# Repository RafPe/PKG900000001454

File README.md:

# Gumstix Raspberry Pi CM4 Uprev
## PKG900000001454 ![][thumbnail]

The **Gumstix Raspberry Pi CM4 Uprev** board allows the Raspberry Pi CM4 COM to be used on existing CM3 boards. The CM4's GPIOs, communications signals, and power pins are re-routed onto a SODIMM edge connection to match the pin-out of the CM3.

__Features Include__:
* Raspberry Pi CM3-compatible SODIMM edge connection
* Power indicator LED

__Links:__
* [AutoDoc Datasheet][autodoc]
* [Specifications][spec]
* [Store Page][store]
* [Schematics and Layout][hardware]

[thumbnail]: https://d3iwea566ns1n1.cloudfront.net/images/product/218b903c5c33ae7da5bafa5d72b35504696c6415.png
[autodoc]: PKG900000001454_AutoDoc.pdf
[spec]: PKG900000001454_SpecSheet.pdf
[store]: https://store.gumstix.com/cm4-uprev/
[hardware]: hardware/hardware.md
[firmware]: firmware/firmware.md

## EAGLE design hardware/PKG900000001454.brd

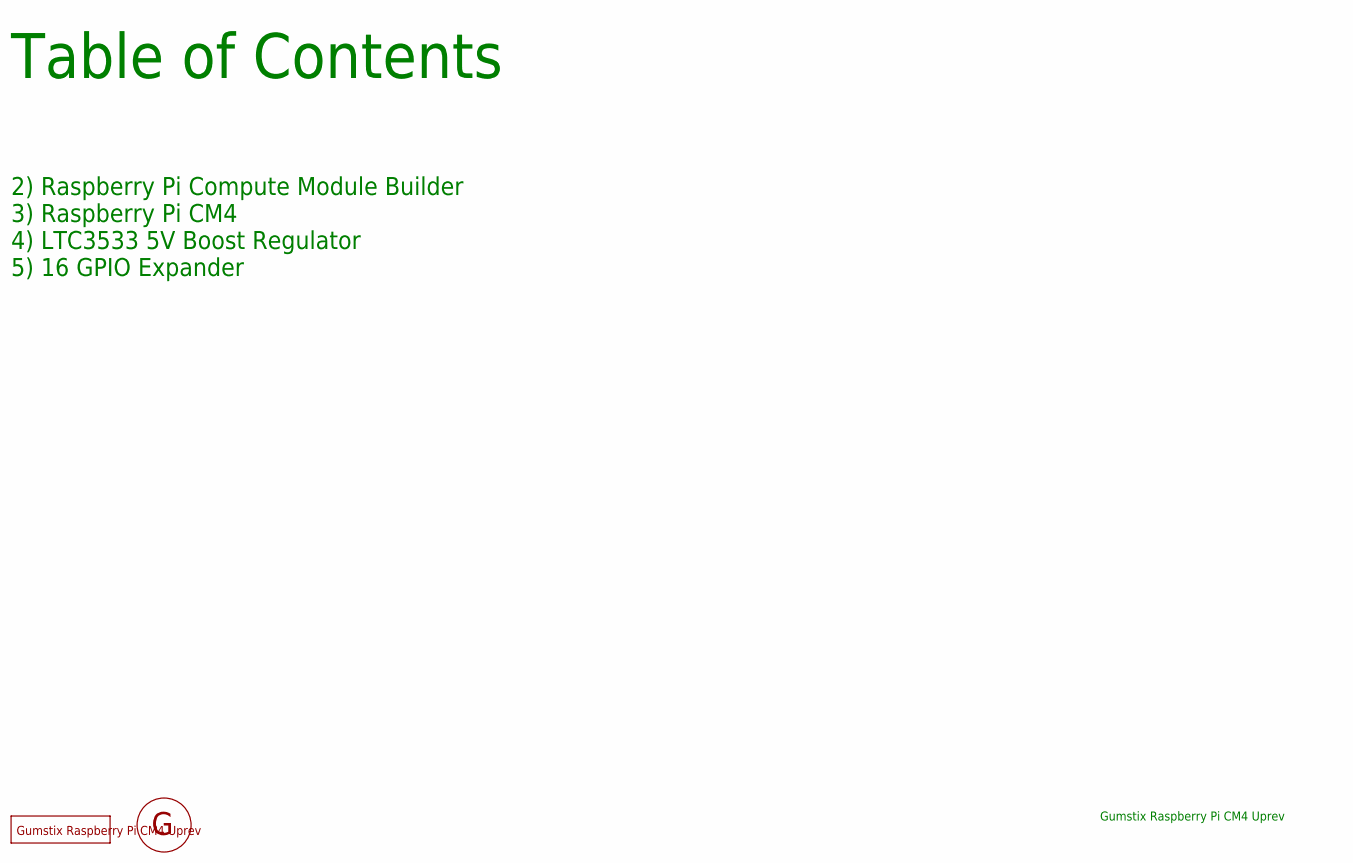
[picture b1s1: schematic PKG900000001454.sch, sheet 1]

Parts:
FD1, FD2, FD3, FD4, FD5, FD6: DNP; FIDUCIAL
U$3: DNP; GEPPETTO_LABEL
U$4: DNP; GEPPETTO_LOGO_SILK10

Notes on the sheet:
Table of Contents
Gumstix Raspberry Pi CM4 Uprev
2) Raspberry Pi Compute Module Builder
3) Raspberry Pi CM4
4) LTC3533 5V Boost Regulator
5) 16 GPIO Expander

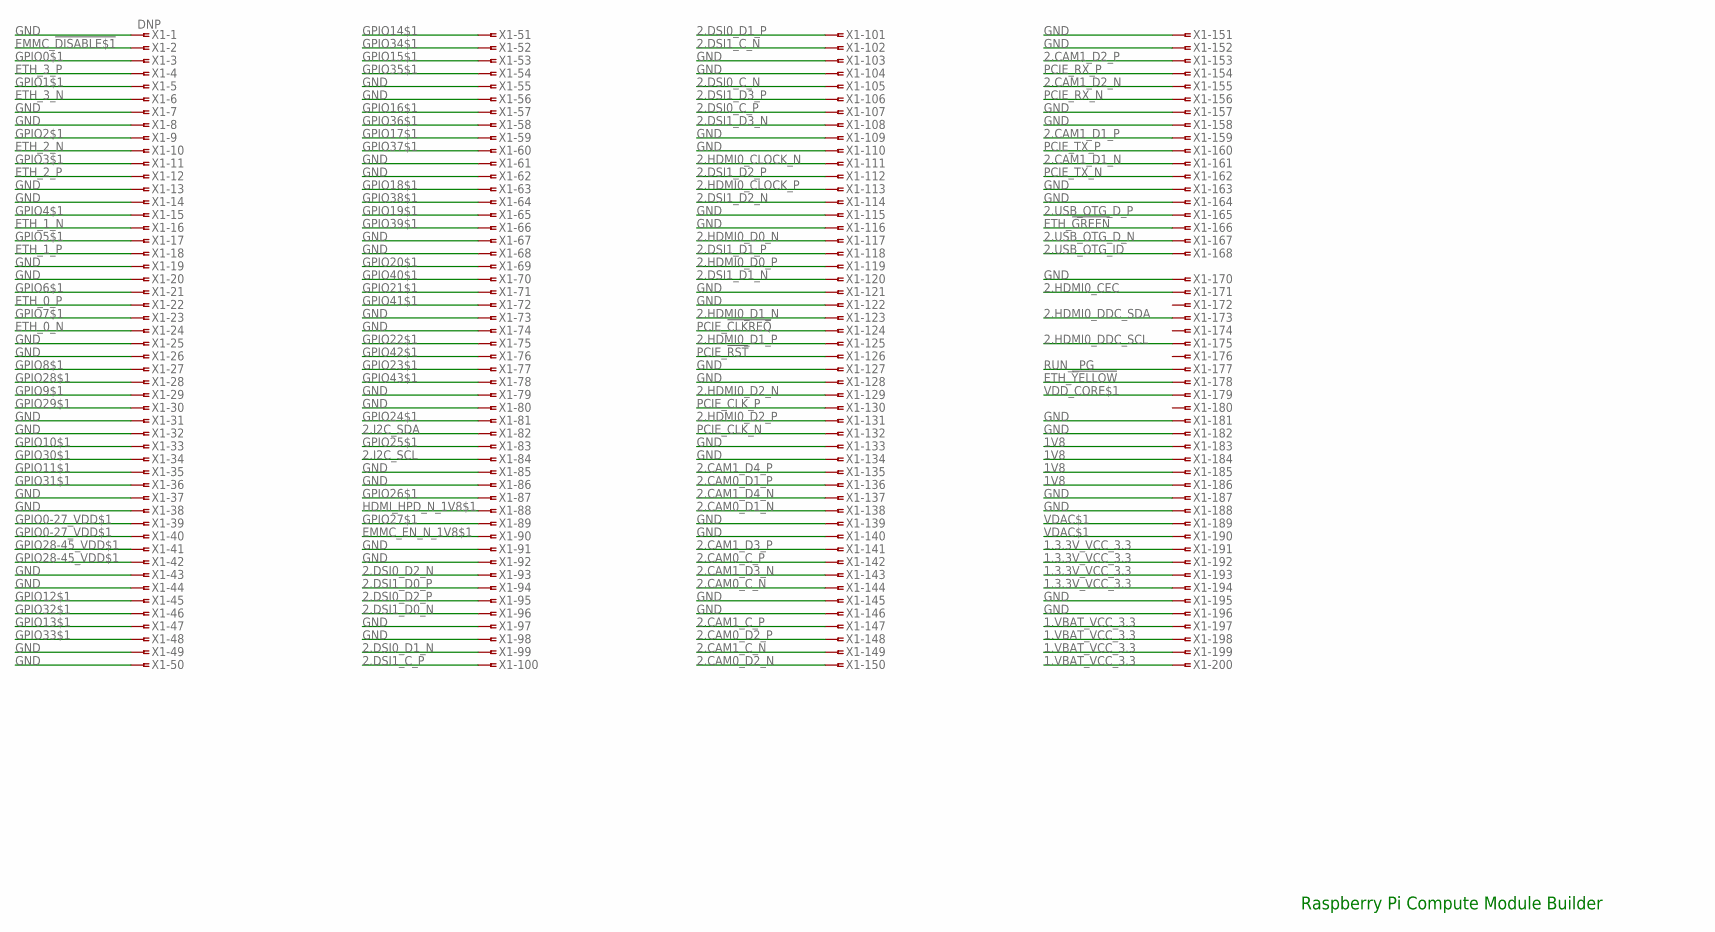
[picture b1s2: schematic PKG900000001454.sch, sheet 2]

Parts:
X1: DNP; SLOT-1376408-1_1.8V_MOD

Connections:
1.3.3V_VCC_3.3: X1.191, X1.192, X1.193, X1.194; also elsewhere on the board
1.VBAT_VCC_3.3: X1.197, X1.198, X1.199, X1.200; also elsewhere on the board
1V8: X1.183, X1.184, X1.185, X1.186
2.CAM0_C_N: X1.144; also elsewhere on the board
2.CAM0_C_P: X1.142; also elsewhere on the board
2.CAM0_D1_N: X1.138; also elsewhere on the board
2.CAM0_D1_P: X1.136; also elsewhere on the board
2.CAM0_D2_N: X1.150; also elsewhere on the board
2.CAM0_D2_P: X1.148; also elsewhere on the board
2.CAM1_C_N: X1.149; also elsewhere on the board
2.CAM1_C_P: X1.147; also elsewhere on the board
2.CAM1_D1_N: X1.161; also elsewhere on the board
2.CAM1_D1_P: X1.159; also elsewhere on the board
2.CAM1_D2_N: X1.155; also elsewhere on the board
2.CAM1_D2_P: X1.153; also elsewhere on the board
2.CAM1_D3_N: X1.143; also elsewhere on the board
2.CAM1_D3_P: X1.141; also elsewhere on the board
2.CAM1_D4_N: X1.137; also elsewhere on the board
2.CAM1_D4_P: X1.135; also elsewhere on the board
2.DSI0_C_N: X1.105; also elsewhere on the board
2.DSI0_C_P: X1.107; also elsewhere on the board
2.DSI0_D1_N: X1.99; also elsewhere on the board
2.DSI0_D1_P: X1.101; also elsewhere on the board
2.DSI0_D2_N: X1.93; also elsewhere on the board
2.DSI0_D2_P: X1.95; also elsewhere on the board
2.DSI1_C_N: X1.102; also elsewhere on the board
2.DSI1_C_P: X1.100; also elsewhere on the board
2.DSI1_D0_N: X1.96; also elsewhere on the board
2.DSI1_D0_P: X1.94; also elsewhere on the board
2.DSI1_D1_N: X1.120; also elsewhere on the board
2.DSI1_D1_P: X1.118; also elsewhere on the board
2.DSI1_D2_N: X1.114; also elsewhere on the board
2.DSI1_D2_P: X1.112; also elsewhere on the board
2.DSI1_D3_N: X1.108; also elsewhere on the board
2.DSI1_D3_P: X1.106; also elsewhere on the board
2.HDMI0_CEC: X1.171; also elsewhere on the board
2.HDMI0_CLOCK_N: X1.111; also elsewhere on the board
2.HDMI0_CLOCK_P: X1.113; also elsewhere on the board
2.HDMI0_D0_N: X1.117; also elsewhere on the board
2.HDMI0_D0_P: X1.119; also elsewhere on the board
2.HDMI0_D1_N: X1.123; also elsewhere on the board
2.HDMI0_D1_P: X1.125; also elsewhere on the board
2.HDMI0_D2_N: X1.129; also elsewhere on the board
2.HDMI0_D2_P: X1.131; also elsewhere on the board
2.HDMI0_DDC_SCL: X1.175; also elsewhere on the board
2.HDMI0_DDC_SDA: X1.173; also elsewhere on the board
2.I2C_SCL: X1.84; also elsewhere on the board
2.I2C_SDA: X1.82; also elsewhere on the board
2.USB_OTG_D_N: X1.167; also elsewhere on the board
2.USB_OTG_D_P: X1.165; also elsewhere on the board
2.USB_OTG_ID: X1.168; also elsewhere on the board
EMMC_!DISABLE$1: X1.2; also elsewhere on the board
EMMC_EN_N_1V8$1: X1.90
ETH_0_N: X1.24; also elsewhere on the board
ETH_0_P: X1.22; also elsewhere on the board
ETH_1_N: X1.16; also elsewhere on the board
ETH_1_P: X1.18; also elsewhere on the board
ETH_2_N: X1.10; also elsewhere on the board
ETH_2_P: X1.12; also elsewhere on the board
ETH_3_N: X1.6; also elsewhere on the board
ETH_3_P: X1.4; also elsewhere on the board
ETH_!GREEN: X1.166; also elsewhere on the board
ETH_!YELLOW: X1.178; also elsewhere on the board
GND: X1.1, X1.7, X1.8, X1.13, X1.14, X1.19, X1.20, X1.25, X1.26, X1.31, X1.32, X1.37, X1.38, X1.43, X1.44, X1.49, X1.50, X1.55, X1.56, X1.61, X1.62, X1.67, X1.68, X1.73, X1.74, X1.79, X1.80, X1.85, X1.86, X1.91, X1.92, X1.97, X1.98, X1.103, X1.104, X1.109, X1.110, X1.115, X1.116, X1.121, X1.122, X1.127, X1.128, X1.133, X1.134, X1.139, X1.140, X1.145, X1.146, X1.151, X1.152, X1.157, X1.158, X1.163, X1.164, X1.170, X1.181, X1.182, X1.187, X1.188, X1.195, X1.196; also elsewhere on the board
GPIO0$1: X1.3; also elsewhere on the board
GPIO0-27_VDD$1: X1.39, X1.40
GPIO1$1: X1.5; also elsewhere on the board
GPIO2$1: X1.9; also elsewhere on the board
GPIO3$1: X1.11; also elsewhere on the board
GPIO4$1: X1.15; also elsewhere on the board
GPIO5$1: X1.17; also elsewhere on the board
GPIO6$1: X1.21; also elsewhere on the board
GPIO7$1: X1.23; also elsewhere on the board
GPIO8$1: X1.27; also elsewhere on the board
GPIO9$1: X1.29; also elsewhere on the board
GPIO10$1: X1.33; also elsewhere on the board
GPIO11$1: X1.35; also elsewhere on the board
GPIO12$1: X1.45; also elsewhere on the board
GPIO13$1: X1.47; also elsewhere on the board
GPIO14$1: X1.51; also elsewhere on the board
GPIO15$1: X1.53; also elsewhere on the board
GPIO16$1: X1.57; also elsewhere on the board
GPIO17$1: X1.59; also elsewhere on the board
GPIO18$1: X1.63; also elsewhere on the board
GPIO19$1: X1.65; also elsewhere on the board
GPIO20$1: X1.69; also elsewhere on the board
GPIO21$1: X1.71; also elsewhere on the board
GPIO22$1: X1.75; also elsewhere on the board
GPIO23$1: X1.77; also elsewhere on the board
GPIO24$1: X1.81; also elsewhere on the board
GPIO25$1: X1.83; also elsewhere on the board
GPIO26$1: X1.87; also elsewhere on the board
GPIO27$1: X1.89; also elsewhere on the board
GPIO28$1: X1.28; also elsewhere on the board
GPIO28-45_VDD$1: X1.41, X1.42
GPIO29$1: X1.30; also elsewhere on the board
GPIO30$1: X1.34; also elsewhere on the board
GPIO31$1: X1.36; also elsewhere on the board
GPIO32$1: X1.46; also elsewhere on the board
GPIO33$1: X1.48; also elsewhere on the board
GPIO34$1: X1.52; also elsewhere on the board
GPIO35$1: X1.54; also elsewhere on the board
GPIO36$1: X1.58; also elsewhere on the board
GPIO37$1: X1.60; also elsewhere on the board
GPIO38$1: X1.64; also elsewhere on the board
GPIO39$1: X1.66; also elsewhere on the board
GPIO40$1: X1.70; also elsewhere on the board
GPIO41$1: X1.72; also elsewhere on the board
GPIO42$1: X1.76; also elsewhere on the board
GPIO43$1: X1.78; also elsewhere on the board
HDMI_HPD_N_1V8$1: X1.88; also elsewhere on the board
PCIE_!CLKREQ: X1.124; also elsewhere on the board
PCIE_!RST: X1.126; also elsewhere on the board
PCIE_CLK_N: X1.132; also elsewhere on the board
PCIE_CLK_P: X1.130; also elsewhere on the board
PCIE_RX_N: X1.156; also elsewhere on the board
PCIE_RX_P: X1.154; also elsewhere on the board
PCIE_TX_N: X1.162; also elsewhere on the board
PCIE_TX_P: X1.160; also elsewhere on the board
RUN__PG: X1.177; also elsewhere on the board
VDAC$1: X1.189, X1.190
VDD_CORE$1: X1.179

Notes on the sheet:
Raspberry Pi Compute Module Builder

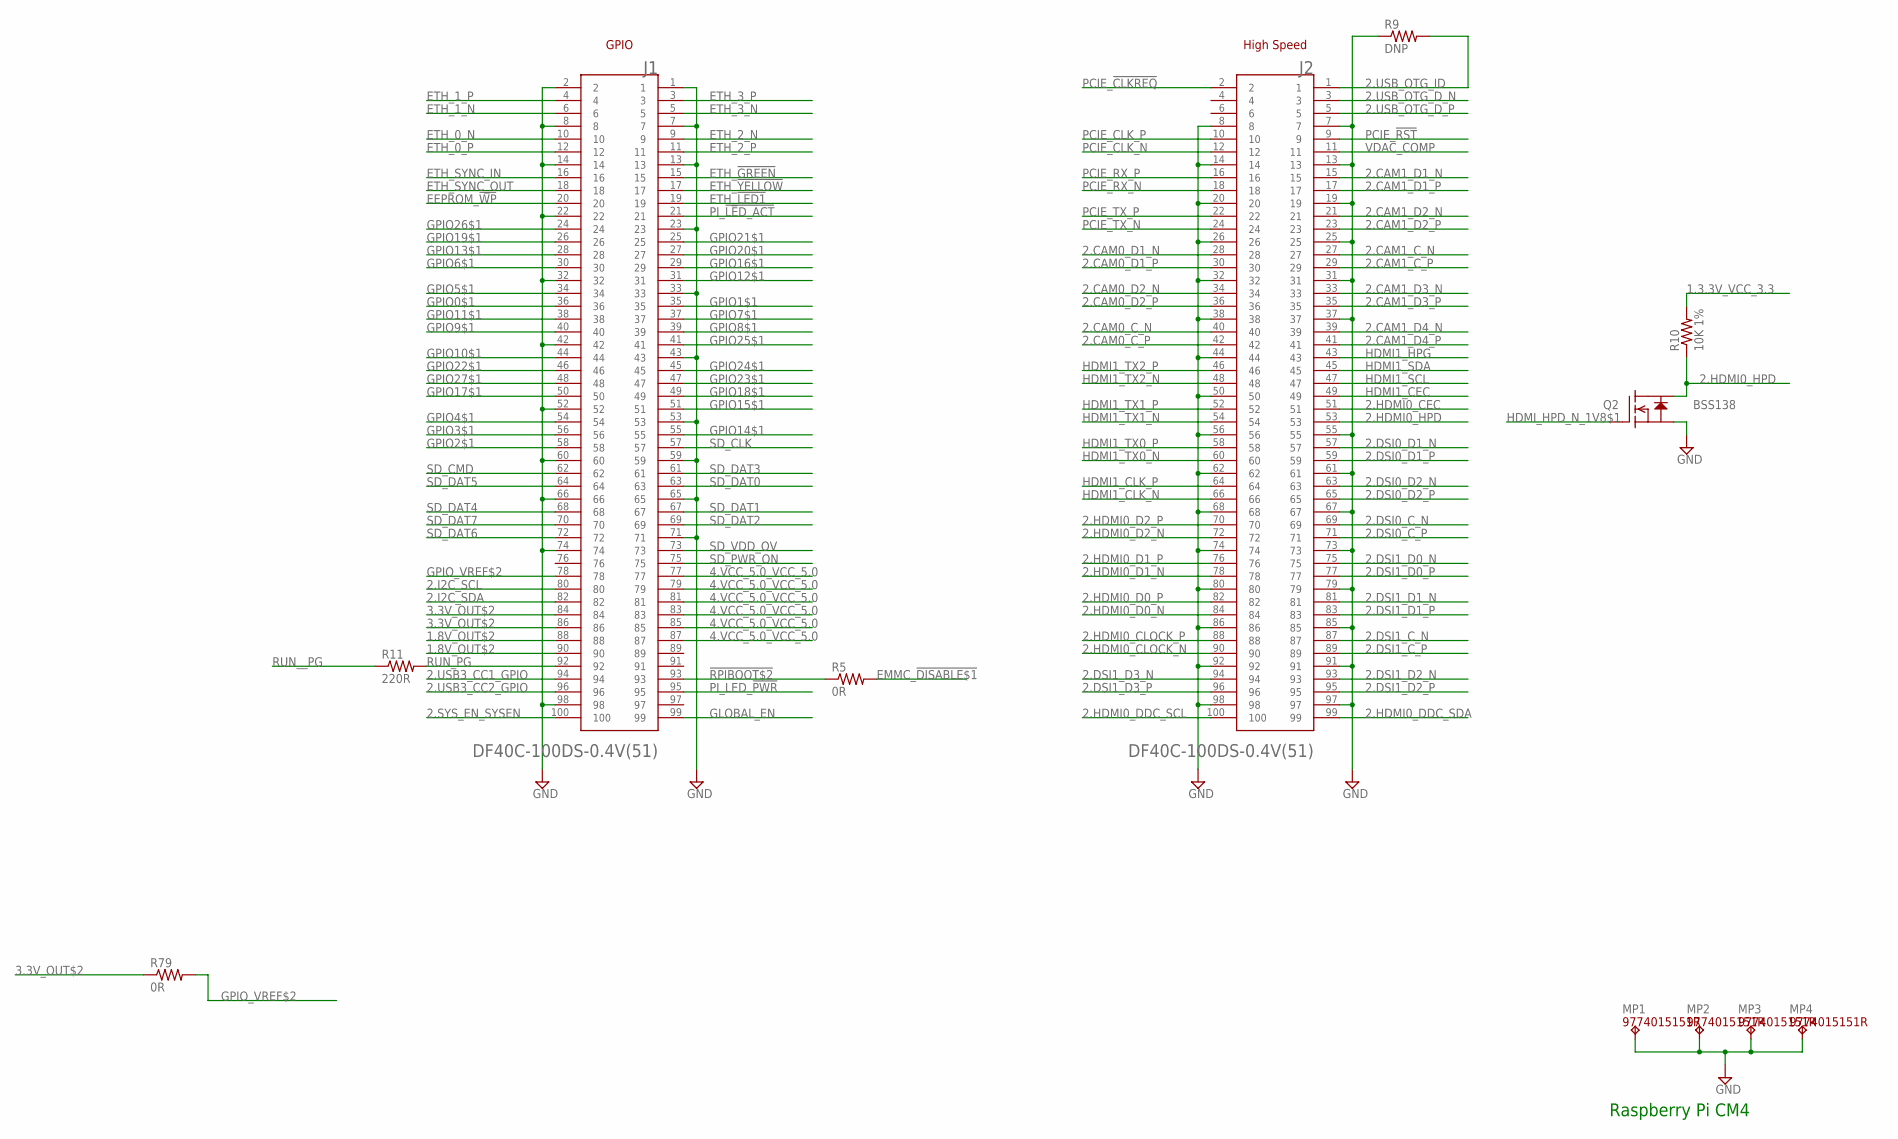
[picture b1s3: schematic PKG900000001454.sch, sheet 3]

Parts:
J1, J2: DF40C-100DS-0.4V(51); HRS_DF40C-100DS-0.4V(51)
MP1, MP2, MP3, MP4: 9774015151R; WA-SMSI_9774___151
Q2: BSS138; SOT23
R5, R79: 0R; 0201
R9: DNP; 0201
R10: 10K 1%; 0201
R11: 220R; 0402

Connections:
1.3.3V_VCC_3.3: R10.2; also elsewhere on the board
1.8V_OUT$2: J1.88, J1.90
2.CAM0_C_N: J2.40; also elsewhere on the board
2.CAM0_C_P: J2.42; also elsewhere on the board
2.CAM0_D1_N: J2.28; also elsewhere on the board
2.CAM0_D1_P: J2.30; also elsewhere on the board
2.CAM0_D2_N: J2.34; also elsewhere on the board
2.CAM0_D2_P: J2.36; also elsewhere on the board
2.CAM1_C_N: J2.27; also elsewhere on the board
2.CAM1_C_P: J2.29; also elsewhere on the board
2.CAM1_D1_N: J2.15; also elsewhere on the board
2.CAM1_D1_P: J2.17; also elsewhere on the board
2.CAM1_D2_N: J2.21; also elsewhere on the board
2.CAM1_D2_P: J2.23; also elsewhere on the board
2.CAM1_D3_N: J2.33; also elsewhere on the board
2.CAM1_D3_P: J2.35; also elsewhere on the board
2.CAM1_D4_N: J2.39; also elsewhere on the board
2.CAM1_D4_P: J2.41; also elsewhere on the board
2.DSI0_C_N: J2.69; also elsewhere on the board
2.DSI0_C_P: J2.71; also elsewhere on the board
2.DSI0_D1_N: J2.57; also elsewhere on the board
2.DSI0_D1_P: J2.59; also elsewhere on the board
2.DSI0_D2_N: J2.63; also elsewhere on the board
2.DSI0_D2_P: J2.65; also elsewhere on the board
2.DSI1_C_N: J2.87; also elsewhere on the board
2.DSI1_C_P: J2.89; also elsewhere on the board
2.DSI1_D0_N: J2.75; also elsewhere on the board
2.DSI1_D0_P: J2.77; also elsewhere on the board
2.DSI1_D1_N: J2.81; also elsewhere on the board
2.DSI1_D1_P: J2.83; also elsewhere on the board
2.DSI1_D2_N: J2.93; also elsewhere on the board
2.DSI1_D2_P: J2.95; also elsewhere on the board
2.DSI1_D3_N: J2.94; also elsewhere on the board
2.DSI1_D3_P: J2.96; also elsewhere on the board
2.HDMI0_CEC: J2.51; also elsewhere on the board
2.HDMI0_CLOCK_N: J2.90; also elsewhere on the board
2.HDMI0_CLOCK_P: J2.88; also elsewhere on the board
2.HDMI0_D0_N: J2.84; also elsewhere on the board
2.HDMI0_D0_P: J2.82; also elsewhere on the board
2.HDMI0_D1_N: J2.78; also elsewhere on the board
2.HDMI0_D1_P: J2.76; also elsewhere on the board
2.HDMI0_D2_N: J2.72; also elsewhere on the board
2.HDMI0_D2_P: J2.70; also elsewhere on the board
2.HDMI0_DDC_SCL: J2.100; also elsewhere on the board
2.HDMI0_DDC_SDA: J2.99; also elsewhere on the board
2.HDMI0_HPD: J2.53, Q2.3 (D), R10.1
2.I2C_SCL: J1.80; also elsewhere on the board
2.I2C_SDA: J1.82; also elsewhere on the board
2.SYS_EN_SYSEN: J1.100
2.USB3_CC1_GPIO: J1.94
2.USB3_CC2_GPIO: J1.96
2.USB_OTG_D_N: J2.3; also elsewhere on the board
2.USB_OTG_D_P: J2.5; also elsewhere on the board
2.USB_OTG_ID: J2.1, R9.2; also elsewhere on the board
3.3V_OUT$2: J1.84, J1.86, R79.1
4.VCC_5.0_VCC_5.0: J1.77, J1.79, J1.81, J1.83, J1.85, J1.87; also elsewhere on the board
!RPIBOOT$2: J1.93, R5.1
EEPROM_!WP: J1.20
EMMC_!DISABLE$1: R5.2; also elsewhere on the board
ETH_0_N: J1.10; also elsewhere on the board
ETH_0_P: J1.12; also elsewhere on the board
ETH_1_N: J1.6; also elsewhere on the board
ETH_1_P: J1.4; also elsewhere on the board
ETH_2_N: J1.9; also elsewhere on the board
ETH_2_P: J1.11; also elsewhere on the board
ETH_3_N: J1.5; also elsewhere on the board
ETH_3_P: J1.3; also elsewhere on the board
ETH_!GREEN: J1.15; also elsewhere on the board
ETH_!LED1: J1.19
ETH_!YELLOW: J1.17; also elsewhere on the board
ETH_SYNC_IN: J1.16
ETH_SYNC_OUT: J1.18
GLOBAL_EN: J1.99
GND: J1.1, J1.2, J1.7, J1.8, J1.13, J1.14, J1.22, J1.23, J1.32, J1.33, J1.42, J1.43, J1.52, J1.53, J1.59, J1.60, J1.65, J1.66, J1.71, J1.74, J1.98, J2.7, J2.8, J2.13, J2.14, J2.19, J2.20, J2.25, J2.26, J2.31, J2.32, J2.37, J2.38, J2.44, J2.50, J2.55, J2.56, J2.61, J2.62, J2.67, J2.68, J2.73, J2.74, J2.79, J2.80, J2.85, J2.86, J2.91, J2.92, J2.97, J2.98, MP1.1, MP2.1, MP3.1, MP4.1, Q2.2 (S), R9.1; also elsewhere on the board
GPIO0$1: J1.36; also elsewhere on the board
GPIO1$1: J1.35; also elsewhere on the board
GPIO2$1: J1.58; also elsewhere on the board
GPIO3$1: J1.56; also elsewhere on the board
GPIO4$1: J1.54; also elsewhere on the board
GPIO5$1: J1.34; also elsewhere on the board
GPIO6$1: J1.30; also elsewhere on the board
GPIO7$1: J1.37; also elsewhere on the board
GPIO8$1: J1.39; also elsewhere on the board
GPIO9$1: J1.40; also elsewhere on the board
GPIO10$1: J1.44; also elsewhere on the board
GPIO11$1: J1.38; also elsewhere on the board
GPIO12$1: J1.31; also elsewhere on the board
GPIO13$1: J1.28; also elsewhere on the board
GPIO14$1: J1.55; also elsewhere on the board
GPIO15$1: J1.51; also elsewhere on the board
GPIO16$1: J1.29; also elsewhere on the board
GPIO17$1: J1.50; also elsewhere on the board
GPIO18$1: J1.49; also elsewhere on the board
GPIO19$1: J1.26; also elsewhere on the board
GPIO20$1: J1.27; also elsewhere on the board
GPIO21$1: J1.25; also elsewhere on the board
GPIO22$1: J1.46; also elsewhere on the board
GPIO23$1: J1.47; also elsewhere on the board
GPIO24$1: J1.45; also elsewhere on the board
GPIO25$1: J1.41; also elsewhere on the board
GPIO26$1: J1.24; also elsewhere on the board
GPIO27$1: J1.48; also elsewhere on the board
GPIO_VREF$2: J1.78, R79.2
HDMI1_CEC: J2.49
HDMI1_CLK_N: J2.66
HDMI1_CLK_P: J2.64
HDMI1_HPG: J2.43
HDMI1_SCL: J2.47
HDMI1_SDA: J2.45
HDMI1_TX0_N: J2.60
HDMI1_TX0_P: J2.58
HDMI1_TX1_N: J2.54
HDMI1_TX1_P: J2.52
HDMI1_TX2_N: J2.48
HDMI1_TX2_P: J2.46
HDMI_HPD_N_1V8$1: Q2.1 (G); also elsewhere on the board
PCIE_!CLKREQ: J2.2; also elsewhere on the board
PCIE_!RST: J2.9; also elsewhere on the board
PCIE_CLK_N: J2.12; also elsewhere on the board
PCIE_CLK_P: J2.10; also elsewhere on the board
PCIE_RX_N: J2.18; also elsewhere on the board
PCIE_RX_P: J2.16; also elsewhere on the board
PCIE_TX_N: J2.24; also elsewhere on the board
PCIE_TX_P: J2.22; also elsewhere on the board
PI_!LED_ACT: J1.21
PI_LED_!PWR: J1.95
RUN_PG: J1.92, R11.2
RUN__PG: R11.1; also elsewhere on the board
SD_CLK: J1.57
SD_CMD: J1.62
SD_DAT0: J1.63
SD_DAT1: J1.67
SD_DAT2: J1.69
SD_DAT3: J1.61
SD_DAT4: J1.68
SD_DAT5: J1.64
SD_DAT6: J1.72
SD_DAT7: J1.70
SD_PWR_ON: J1.75
SD_VDD_OV: J1.73
VDAC_COMP: J2.11

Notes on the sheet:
Raspberry Pi CM4
GPIO
High Speed

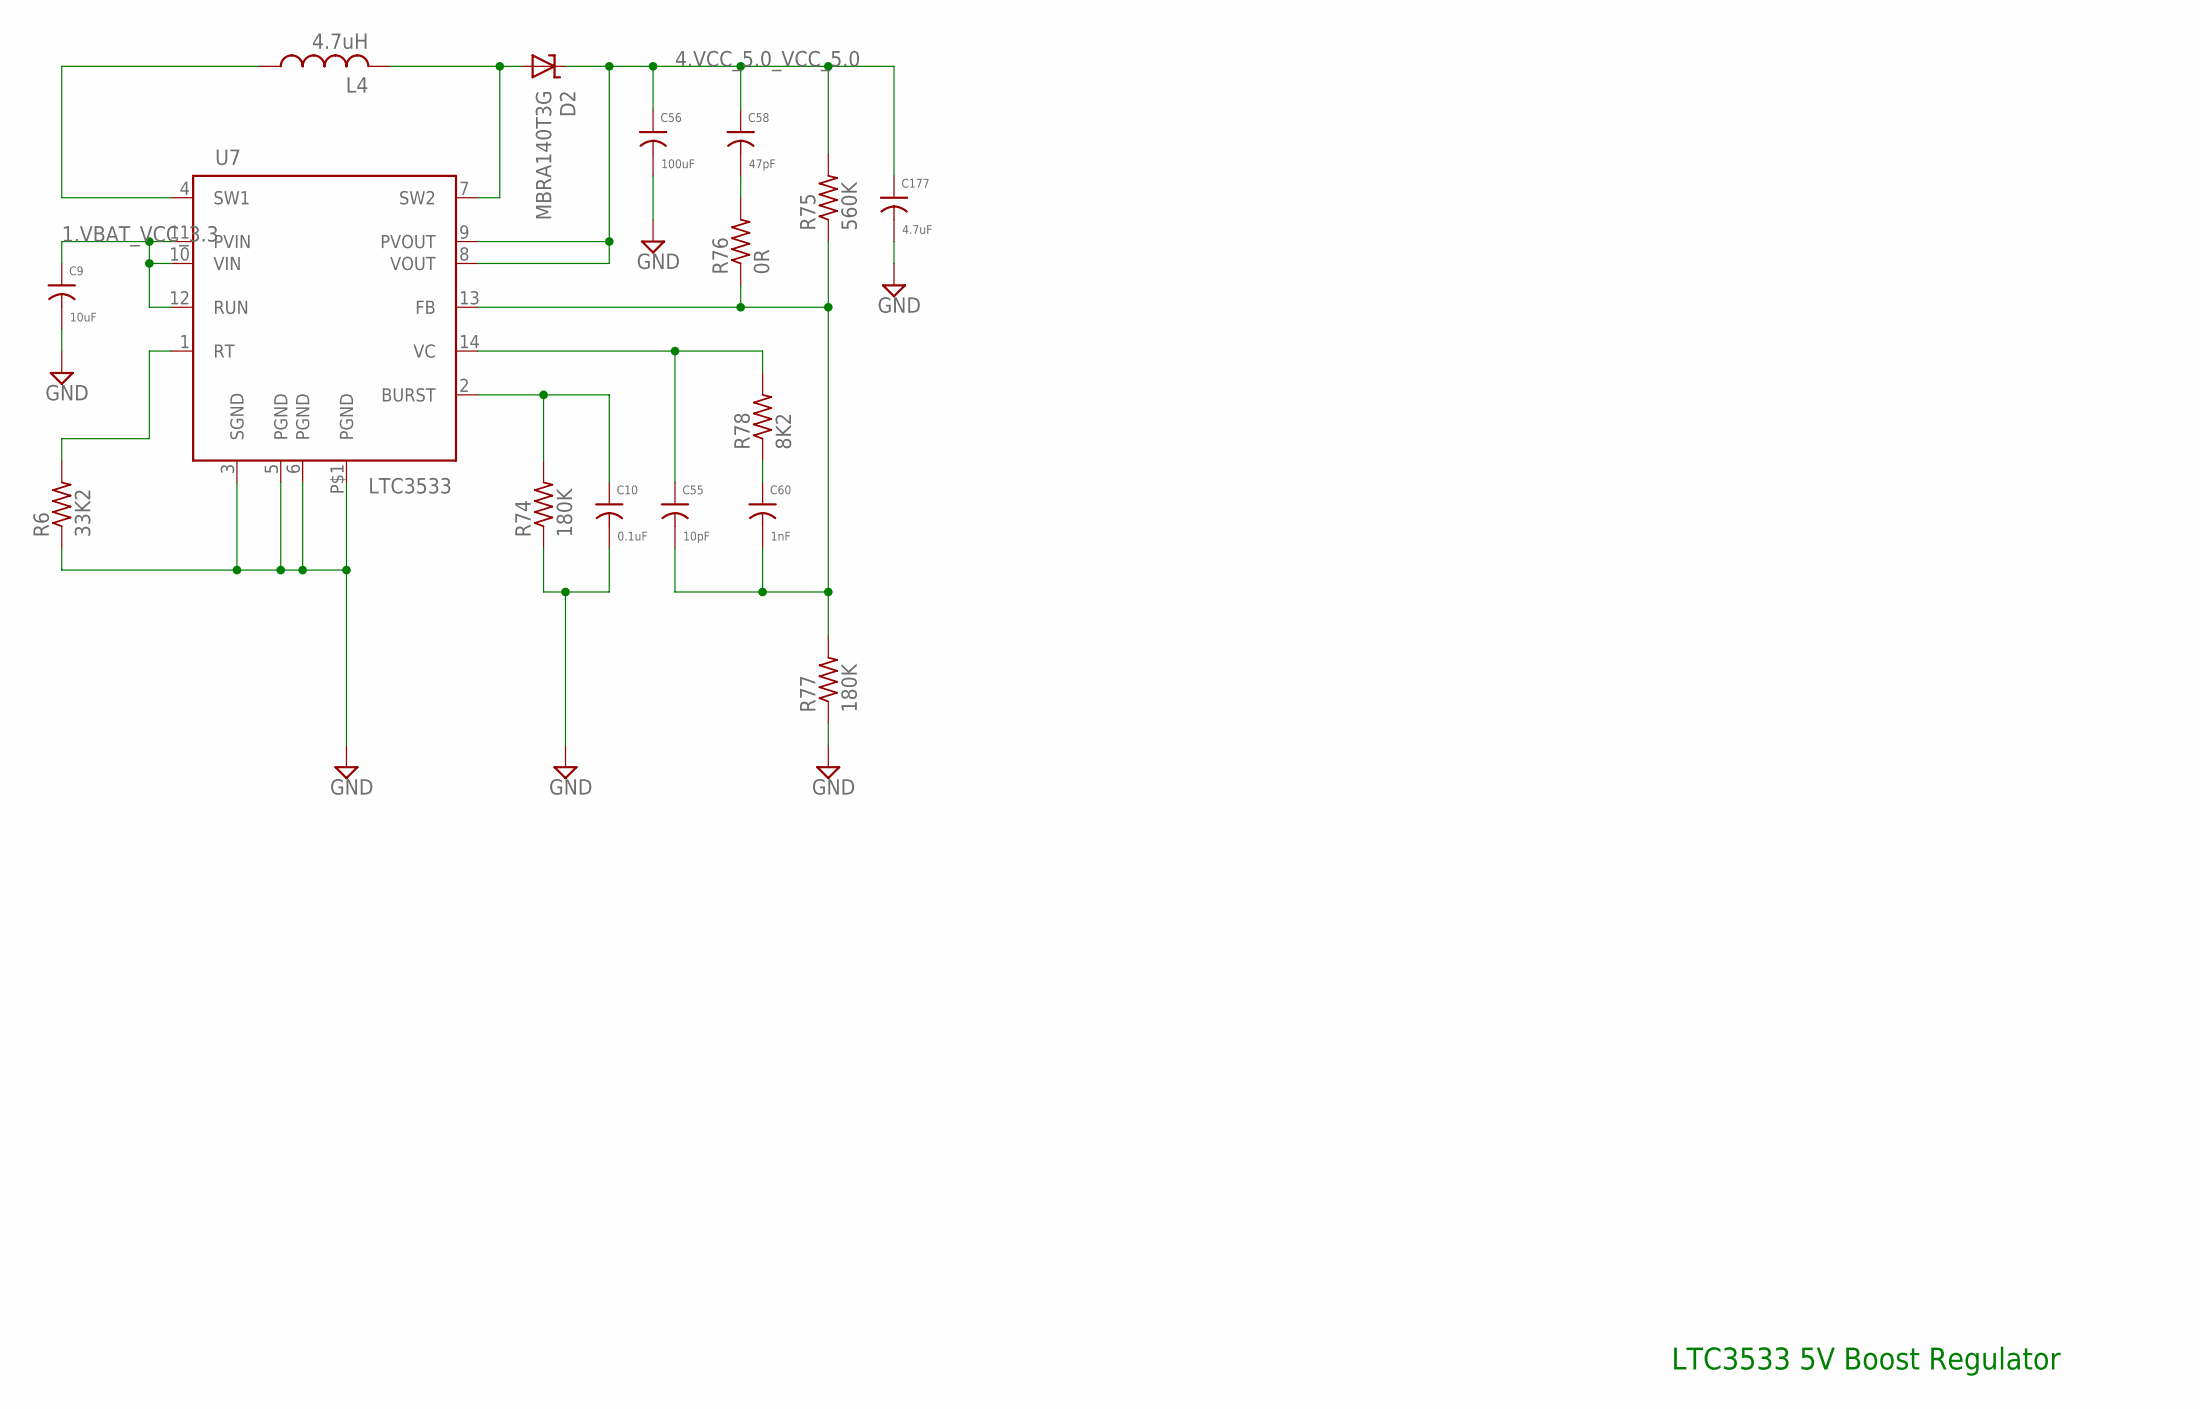
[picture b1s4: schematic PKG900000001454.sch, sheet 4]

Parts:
C9: 10uF; 0603
C10: 0.1uF; 0201
C55: 10pF; 0201
C56: 100uF; 1206
C58: 47pF; 0201
C60: 1nF; 0402
C177: 4.7uF; 0603
D2: MBRA140T3G; SMAJ
L4: 4.7uH; B82462
R6: 33K2; 0402
R74, R77: 180K; 0201
R75: 560K; 0402
R76: 0R; 0201
R78: 8K2; 0402
U7: LTC3533; DFN-14

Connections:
1.VBAT_VCC_3.3: C9.1, U7.10 (VIN), U7.11 (PVIN), U7.12 (RUN); also elsewhere on the board
4.VCC_5.0_VCC_5.0: C56.1, C58.1, C177.1, D2.C, R75.2, U7.8 (VOUT), U7.9 (PVOUT); also elsewhere on the board
BURST$3: C10.1, R74.2, U7.2 (BURST)
FB_5$3: C55.2, C60.2, R75.1, R76.1, R77.2, U7.13 (FB)
FB_5A$3: C58.2, R76.2
GND: C9.2, C10.2, C56.2, C177.2, R6.1, R74.1, R77.1, U7.3 (SGND), U7.5 (PGND), U7.6 (PGND), U7.P$1 (PGND); also elsewhere on the board
PRE_FB$3: C60.1, R78.1
RT$3: R6.2, U7.1 (RT)
SW1$3: L4.1, U7.4 (SW1)
SW2$3: D2.A, L4.2, U7.7 (SW2)
VC$3: C55.1, R78.2, U7.14 (VC)

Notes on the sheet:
LTC3533 5V Boost Regulator

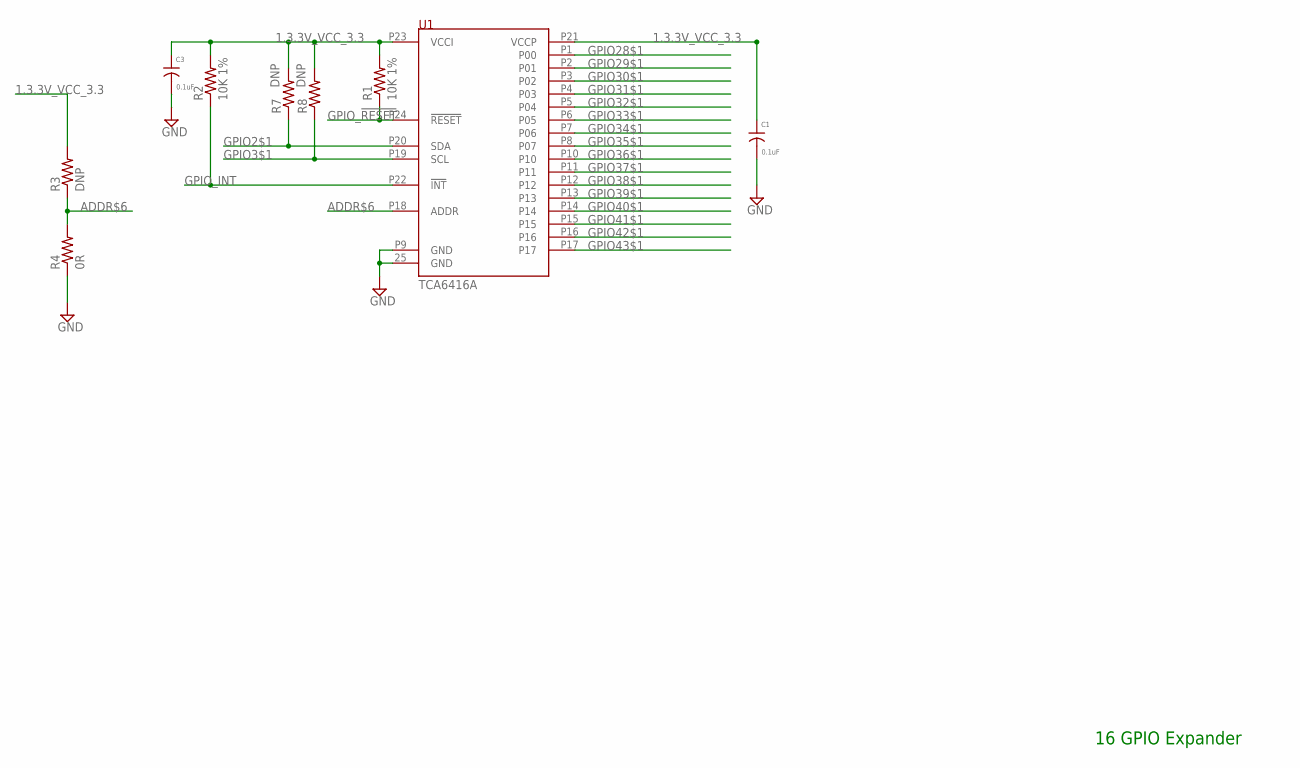
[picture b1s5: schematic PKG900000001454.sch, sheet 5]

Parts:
C1, C3: 0.1uF; 0201
R1, R2: 10K 1%; 0201
R3, R7, R8: DNP; 0201
R4: 0R; 0201
U1: TCA6416A; WQFN24

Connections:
1.3.3V_VCC_3.3: C1.1, C3.1, R1.2, R2.2, R3.2, R7.2, R8.2, U1.P21 (VCCP), U1.P23 (VCCI); also elsewhere on the board
ADDR$6: R3.1, R4.2, U1.P18 (ADDR)
GND: C1.2, C3.2, R4.1, U1.25 (GND), U1.P9 (GND); also elsewhere on the board
GPIO2$1: R7.1, U1.P20 (SDA); also elsewhere on the board
GPIO3$1: R8.1, U1.P19 (SCL); also elsewhere on the board
GPIO28$1: U1.P1 (P00); also elsewhere on the board
GPIO29$1: U1.P2 (P01); also elsewhere on the board
GPIO30$1: U1.P3 (P02); also elsewhere on the board
GPIO31$1: U1.P4 (P03); also elsewhere on the board
GPIO32$1: U1.P5 (P04); also elsewhere on the board
GPIO33$1: U1.P6 (P05); also elsewhere on the board
GPIO34$1: U1.P7 (P06); also elsewhere on the board
GPIO35$1: U1.P8 (P07); also elsewhere on the board
GPIO36$1: U1.P10; also elsewhere on the board
GPIO37$1: U1.P11; also elsewhere on the board
GPIO38$1: U1.P12; also elsewhere on the board
GPIO39$1: U1.P13; also elsewhere on the board
GPIO40$1: U1.P14; also elsewhere on the board
GPIO41$1: U1.P15; also elsewhere on the board
GPIO42$1: U1.P16; also elsewhere on the board
GPIO43$1: U1.P17; also elsewhere on the board
GPIO_!RESET: R1.1, U1.P24 (!RESET!)
GPIO_INT: R2.1, U1.P22 (!INT!)

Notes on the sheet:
16 GPIO Expander

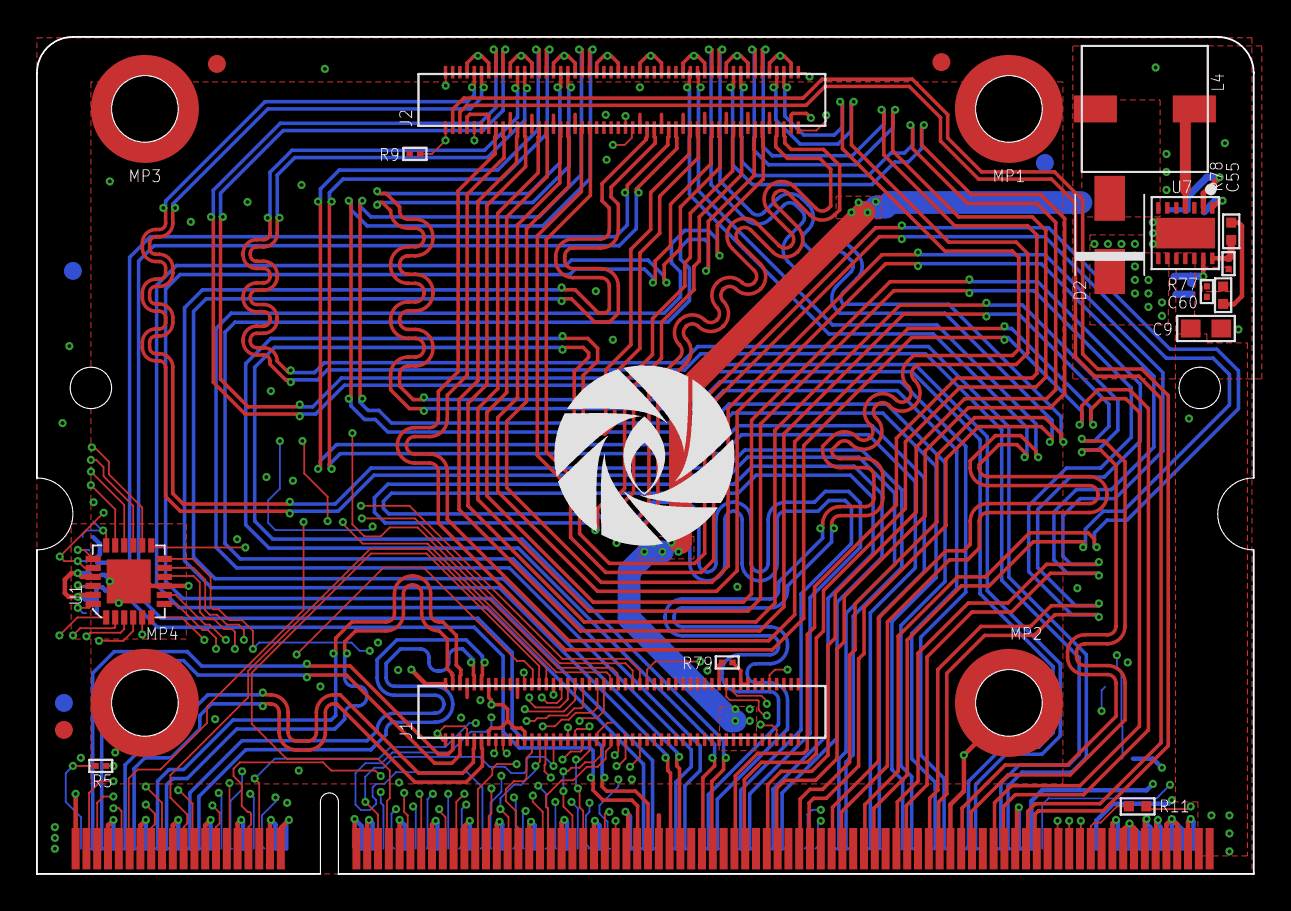
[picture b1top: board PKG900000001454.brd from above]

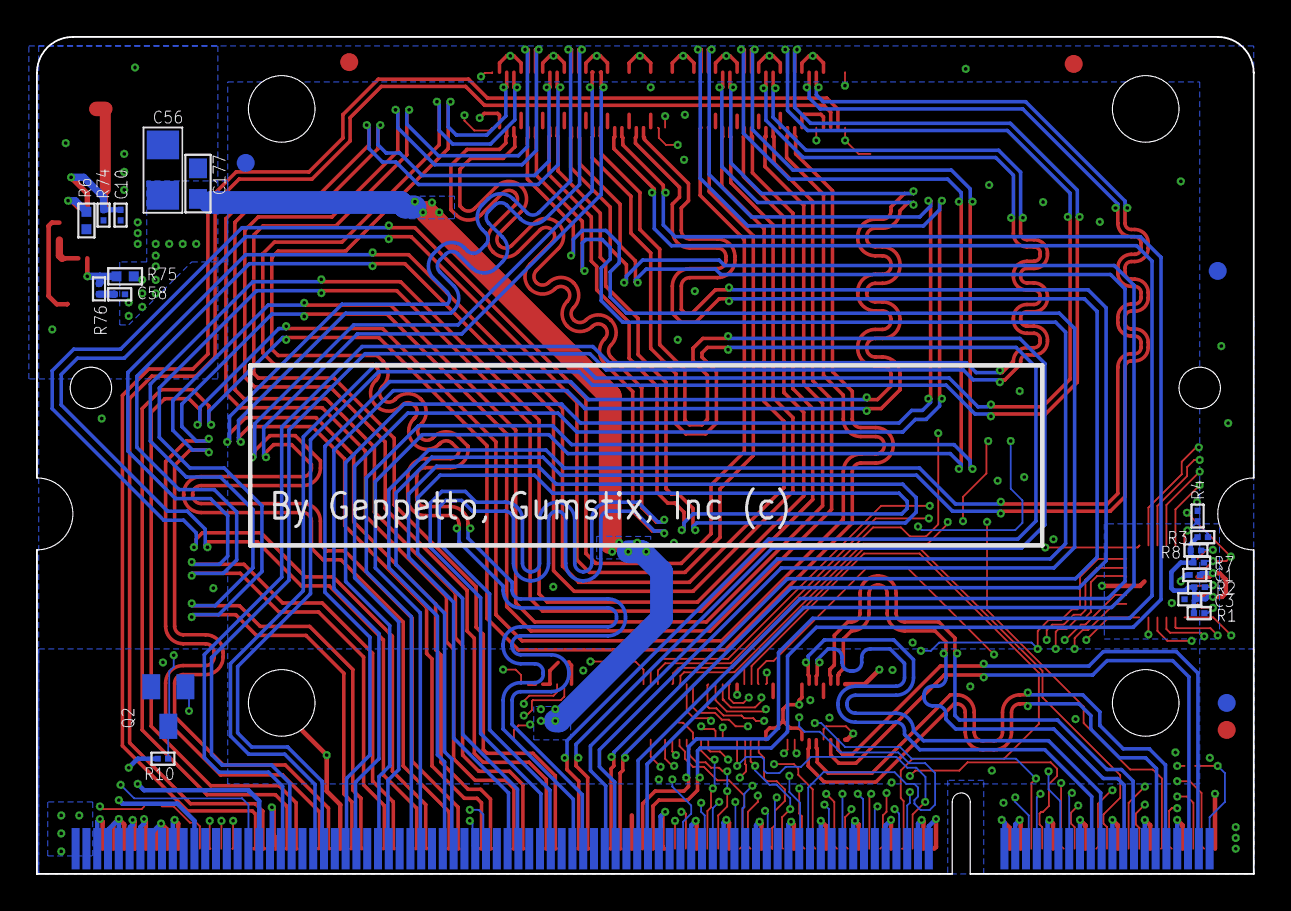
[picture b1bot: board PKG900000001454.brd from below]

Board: 6 copper layers, 67.6 x 46.5 mm, 46 parts (22 on the bottom side), 138 nets.

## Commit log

2020-10-13 Add README content, spec sheet, autodoc and folders
2020-10-15 Added hardware documents for revision 2.
2020-10-15 add links to sch and brd

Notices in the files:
parts and their libraries:
qualified_1: COMPANY_AND_YEAR: Geppetto, Gumstix Inc (c) 2019
